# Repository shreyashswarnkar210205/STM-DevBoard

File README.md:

# ⚡ STM-OWN – Custom STM32 Development Board

Custom STM32-based development board designed in **KiCad** for learning and experimenting with embedded systems and PCB design.

This project demonstrates the complete PCB design workflow including schematic design, PCB layout, custom footprint creation, and hardware documentation.

---

## 🧠 Project Overview

**STM-OWN** is a custom STM32 development board inspired by common development boards such as Bluepill and Nucleo boards.

The objective of this project was to practice:

- STM32 hardware design
- Schematic capture
- PCB layout and routing
- Creating custom KiCad libraries
- Generating manufacturing-ready files
- Hardware documentation

This board can be used for:

- Embedded firmware development
- Peripheral interfacing
- Learning STM32 architecture
- Rapid prototyping

---

## 🛠 Tools Used

- **KiCad** – Schematic capture and PCB design
- **Custom symbol libraries**
- **Custom footprint libraries**
- **Git & GitHub** – Version control
- **PDF exports** – Documentation

---

## 🏗 PCB Design

Features of the board include:

- STM32 microcontroller core
- GPIO breakout headers
- Power regulation circuitry
- Programming/debug interface
- User interface components (buttons / LEDs)

Design considerations:

- Proper decoupling capacitors
- Clean power routing
- Ground plane usage
- Optimized component placement
- Design Rule Check (DRC) compliance

---

## 🖼 Board Preview

### Front View

### Back View

### 3D View

---

## 📂 Repository Structure
STM-OWN
│
├── Main/ # KiCad project files
│ ├── Main.kicad_pcb
│ ├── Main.kicad_pro
│ └── backups/
│
├── SIGN.pretty/ # Custom footprint library
│
├── FRONT.png # PCB front render
├── BACK.png # PCB back render
├── ANGLE-1.png # 3D board view
├── ANGLE-2.png # 3D board view
│
├── Schematic.pdf # Full schematic
├── Layout.pdf # PCB layout documentation
├── Basic.pdf # Design notes
│
└── README.md

---

## 📑 Documentation

Included design documentation:

- **Schematic.pdf** – Full circuit schematic
- **Layout.pdf** – PCB layout visualization
- **Basic.pdf** – Additional design notes

These files allow quick viewing of the design without opening KiCad.

---

## 🎯 Learning Outcomes

Through this project:

- Designed a complete STM32 hardware platform
- Learned PCB routing and layout techniques
- Created custom KiCad footprints and symbols
- Generated fabrication-ready design files
- Practiced professional hardware documentation

---

## 🚀 Future Improvements

Possible upgrades for the next revision:

- Add USB programming interface
- Add SWD debugging header
- Improve power regulation efficiency
- Add additional peripheral connectors
- Convert to a 4-layer PCB design

---

## 📜 License

This project is open hardware and available for educational and experimental use.

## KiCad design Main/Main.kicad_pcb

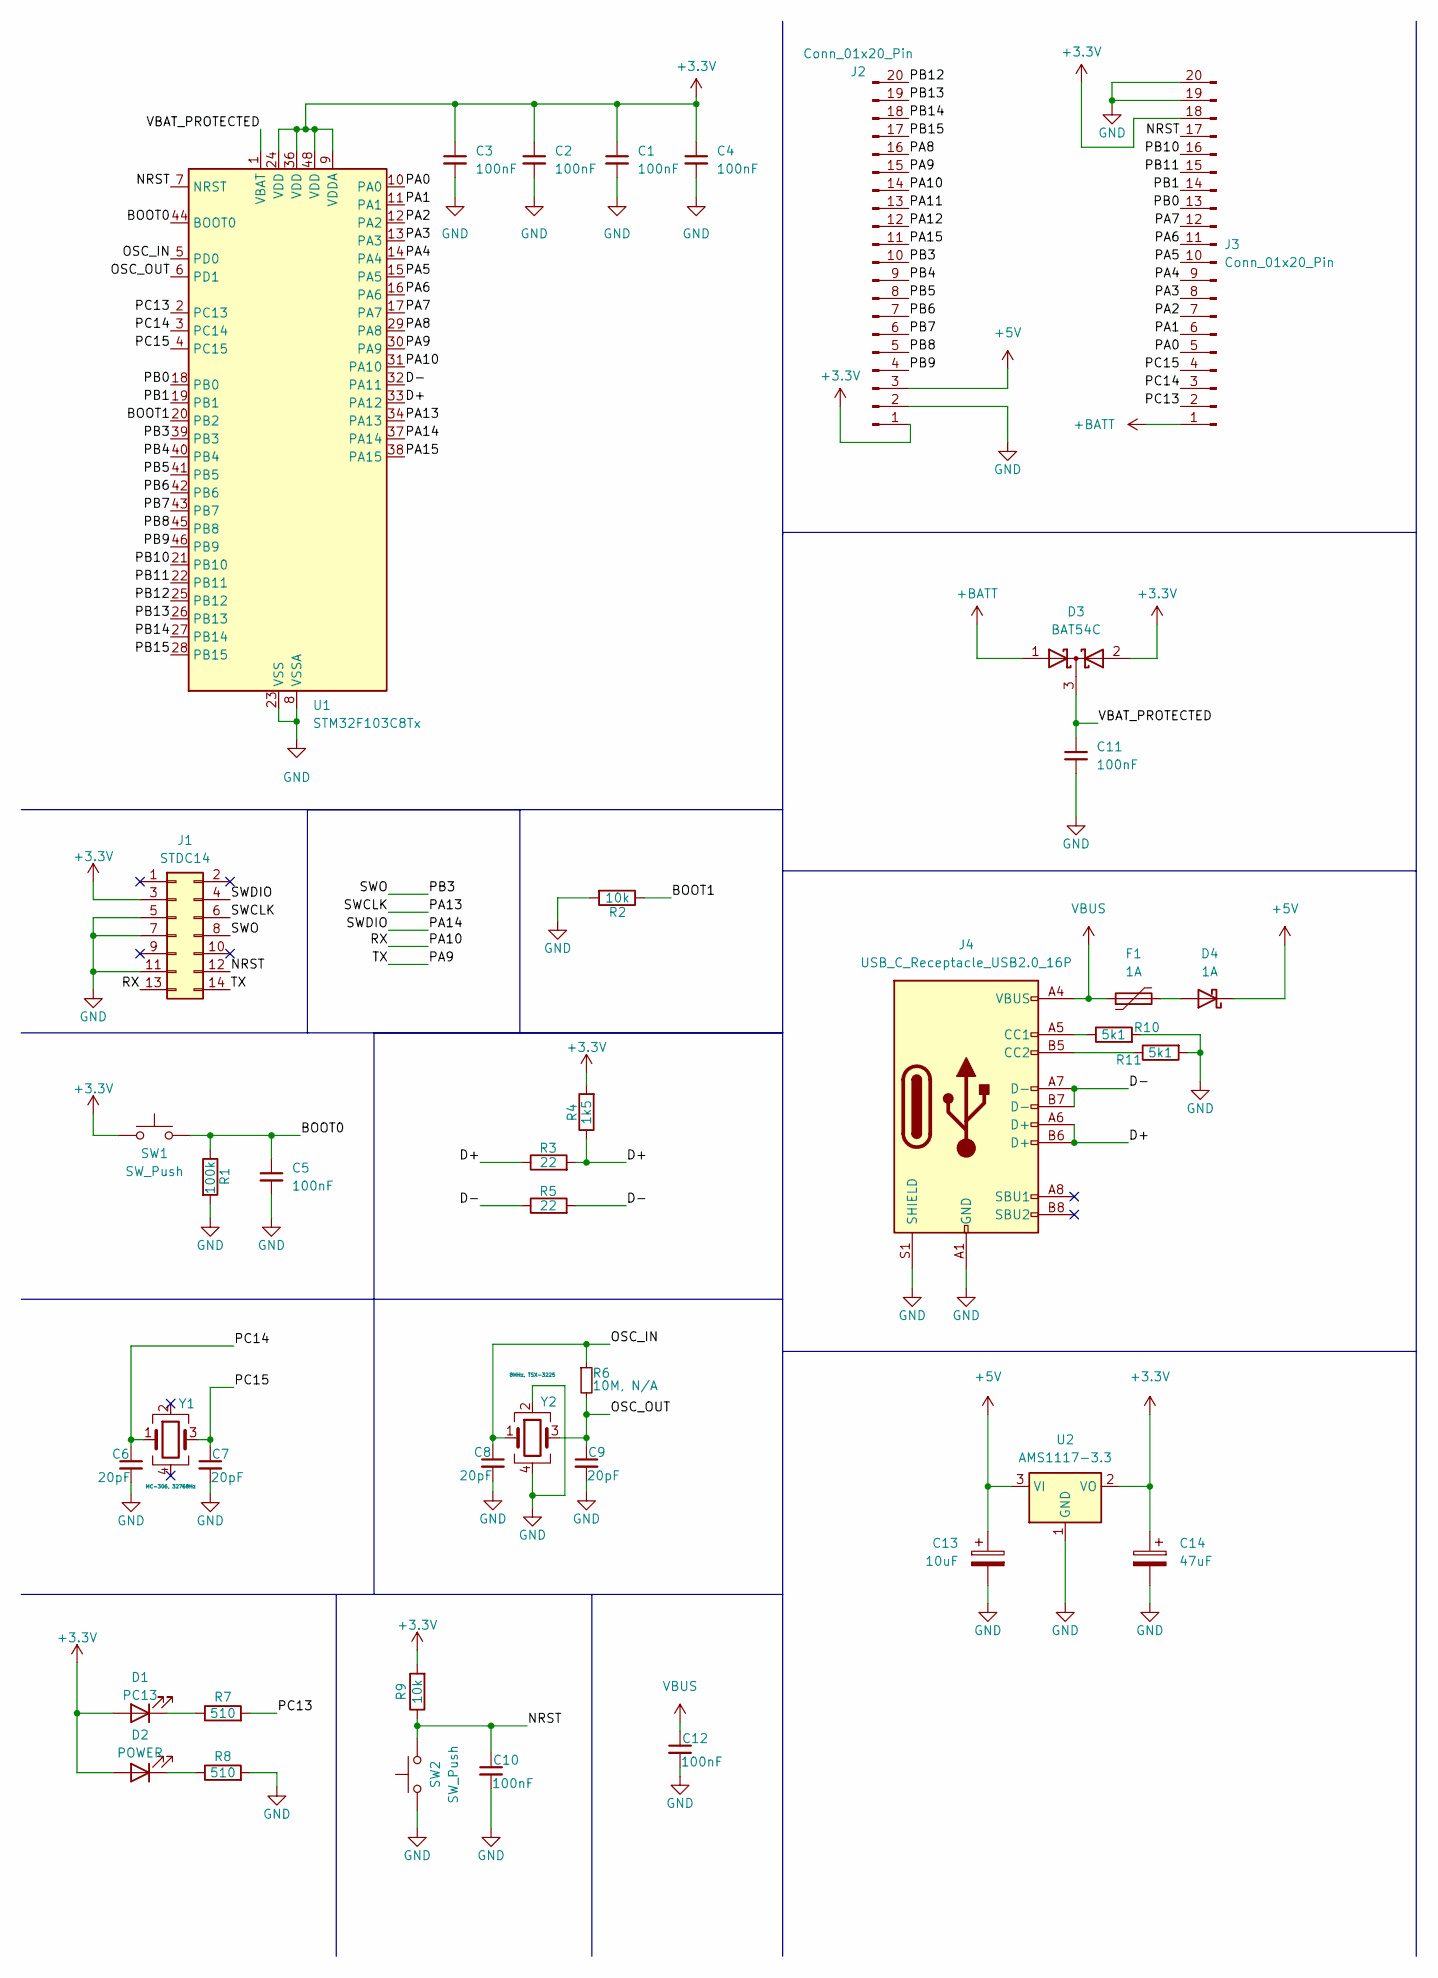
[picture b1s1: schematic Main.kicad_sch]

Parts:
C1, C2, C3, C4, C5, C10, C11, C12: 100nF; C_0402_1005Metric
C6, C7, C8, C9: 20pF; C_0402_1005Metric
C13: 10uF; CP_EIA-1608-08_AVX-J
C14: 47uF; CP_EIA-1608-08_AVX-J
D1: PC13; LED_2010_5025Metric
D2: POWER; LED_2010_5025Metric
D3: BAT54C; SOT-23
D4: 1A; D_1812_4532Metric_Pad1.30x3.40mm_HandSolder
F1: 1A; D_1812_4532Metric_Pad1.30x3.40mm_HandSolder
J1: STDC14; PinSocket_2x07_P2.54mm_Vertical
J2, J3: Conn_01x20_Pin; PinSocket_1x20_P2.54mm_Vertical
J4: USB_C_Receptacle_USB2.0_16P; USB_C_Receptacle_GCT_USB4105-xx-A_16P_TopMnt_Horizontal
R1: 100k; R_0201_0603Metric_Pad0.64x0.40mm_HandSolder
R2, R9: 10k; R_0201_0603Metric_Pad0.64x0.40mm_HandSolder
R3, R5: 22; R_0201_0603Metric_Pad0.64x0.40mm_HandSolder
R4: 1k5; R_0201_0603Metric_Pad0.64x0.40mm_HandSolder
R6: 10M, N/A; R_0201_0603Metric_Pad0.64x0.40mm_HandSolder
R7, R8: 510; R_0201_0603Metric_Pad0.64x0.40mm_HandSolder
R10, R11: 5k1; R_0201_0603Metric_Pad0.64x0.40mm_HandSolder
SW1, SW2: SW_Push; SW_Push_1P1T_NO_CK_KMR2
U1: STM32F103C8Tx; LQFP-48_7x7mm_P0.5mm
U2: AMS1117-3.3; SOT-223-3_TabPin2
Y1: MC-306, 32768Hz; Oscillator_SMD_Abracon_ASE-4Pin_3.2x2.5mm_HandSoldering
Y2: 8MHz, TSX-3225; Oscillator_SMD_Abracon_ASE-4Pin_3.2x2.5mm_HandSoldering

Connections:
+3.3V: C1.1, C2.1, C3.1, C4.1, C14.1, D1.2 (A), D2.2 (A), D3.2 (A), J1.3, J2.1, J3.18, R4.2, R9.2, SW1.1, U1.9 (VDDA), U1.24 (VDD), U1.36 (VDD), U1.48 (VDD), U2.2 (VO)
+5V: C13.1, D4.1 (K), J2.3, U2.3 (VI)
+BATT: D3.1 (A), J3.1
/BOOT0: C5.1, R1.1, SW1.2, U1.44 (BOOT0)
/BOOT1: R2.1, U1.20 (PB2)
/D+: J4.A6 (D+), J4.B6 (D+), R3.1, R3.2, R4.1, U1.33 (PA12)
/D-: J4.A7 (D-), J4.B7 (D-), R5.1, R5.2, U1.32 (PA11)
/NRST: C10.1, J1.12, J3.17, R9.1, SW2.2, U1.7 (NRST)
/OSC_IN: C8.1, R6.1, U1.5 (PD0), Y2.1
/OSC_OUT: C9.1, R6.2, U1.6 (PD1), Y2.3
/PA0: J3.5, U1.10 (PA0)
/PA1: J3.6, U1.11 (PA1)
/PA2: J3.7, U1.12 (PA2)
/PA3: J3.8, U1.13 (PA3)
/PA4: J3.9, U1.14 (PA4)
/PA5: J3.10, U1.15 (PA5)
/PA6: J3.11, U1.16 (PA6)
/PA7: J3.12, U1.17 (PA7)
/PA8: J2.16, U1.29 (PA8)
/PA9: J1.14, J2.15, U1.30 (PA9)
/PA10: J1.13, J2.14, U1.31 (PA10)
/PA11: J2.13
/PA12: J2.12
/PA13: J1.6, U1.34 (PA13)
/PA14: J1.4, U1.37 (PA14)
/PA15: J2.11, U1.38 (PA15)
/PB0: J3.13, U1.18 (PB0)
/PB1: J3.14, U1.19 (PB1)
/PB3: J1.8, J2.10, U1.39 (PB3)
/PB4: J2.9, U1.40 (PB4)
/PB5: J2.8, U1.41 (PB5)
/PB6: J2.7, U1.42 (PB6)
/PB7: J2.6, U1.43 (PB7)
/PB8: J2.5, U1.45 (PB8)
/PB9: J2.4, U1.46 (PB9)
/PB10: J3.16, U1.21 (PB10)
/PB11: J3.15, U1.22 (PB11)
/PB12: J2.20, U1.25 (PB12)
/PB13: J2.19, U1.26 (PB13)
/PB14: J2.18, U1.27 (PB14)
/PB15: J2.17, U1.28 (PB15)
/PC13: J3.2, R7.2, U1.2 (PC13)
/PC14: C6.1, J3.3, U1.3 (PC14), Y1.1
/PC15: C7.1, J3.4, U1.4 (PC15), Y1.3
/VBAT_PROTECTED: C11.1, D3.3 (K), U1.1 (VBAT)
GND: C1.2, C2.2, C3.2, C4.2, C5.2, C6.2, C7.2, C8.2, C9.2, C10.2, C11.2, C12.2, C13.2, C14.2, J1.5, J1.7, J1.11, J2.2, J3.19, J3.20, J4.A1 (GND), J4.A12 (GND), J4.B1 (GND), J4.B12 (GND), J4.S1 (SHIELD), R1.2, R2.2, R8.2, R10.2, R11.2, SW2.1, U1.8 (VSSA), U1.23 (VSS), U1.35 (VSS), U1.47 (VSS), U2.1 (GND), Y2.2, Y2.4
unnamed: D1.1 (K), R7.1
unnamed: D2.1 (K), R8.1
unnamed: D4.2 (A), F1.2
unnamed: J4.A5 (CC1), R10.1
unnamed: J4.B5 (CC2), R11.1
VBUS: C12.1, F1.1, J4.A4 (VBUS), J4.A9 (VBUS), J4.B4 (VBUS), J4.B9 (VBUS)

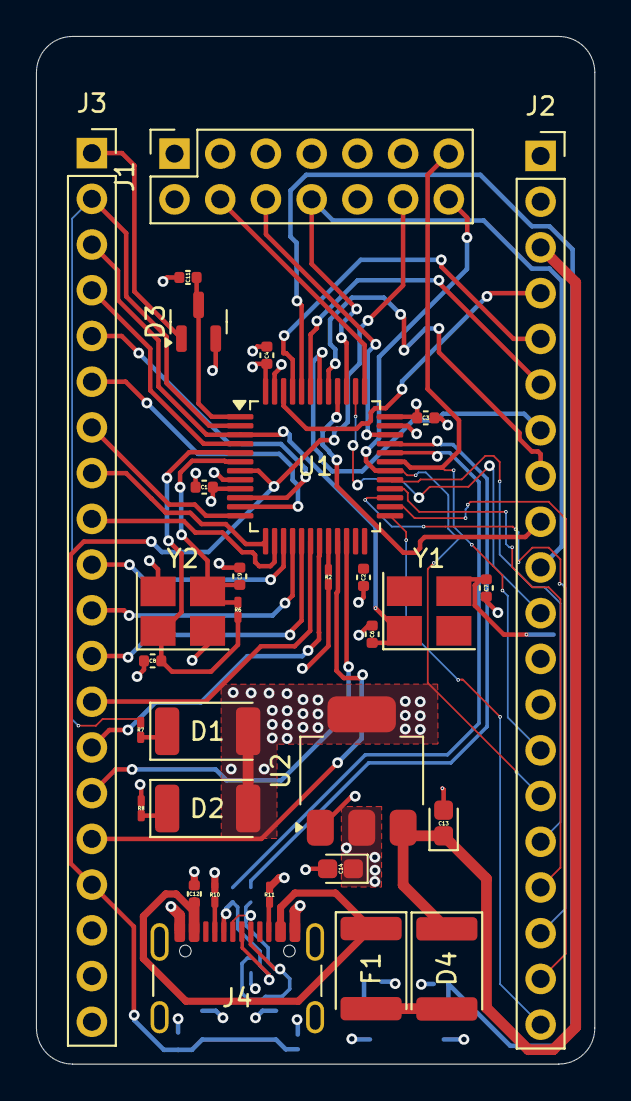
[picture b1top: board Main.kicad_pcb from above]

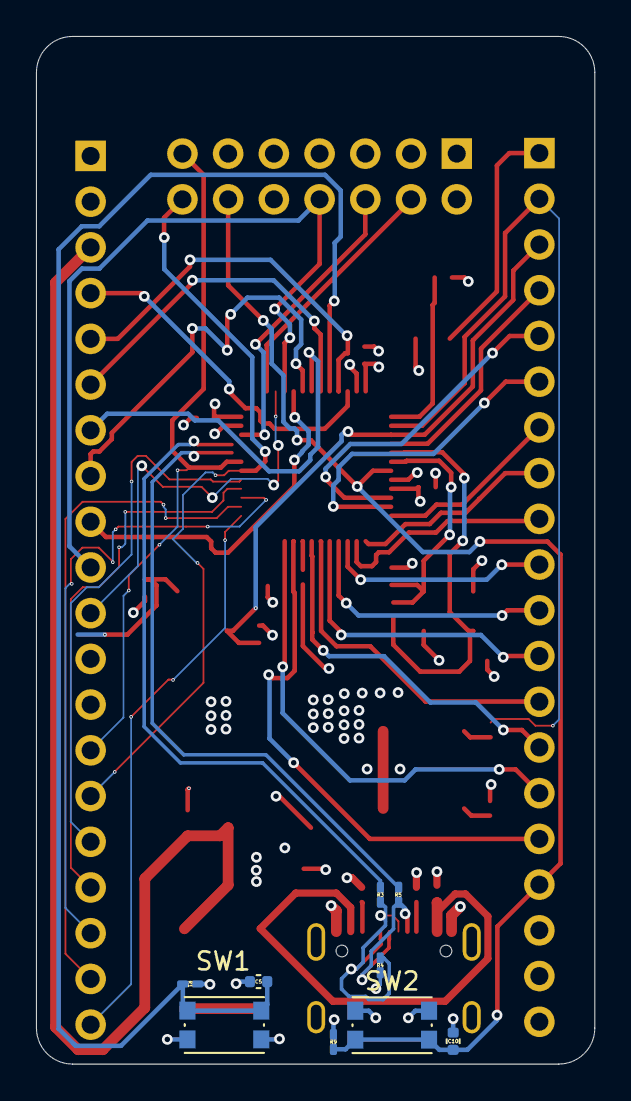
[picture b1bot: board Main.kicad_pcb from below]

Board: 4 copper layers, 31.0 x 57.1 mm, 40 parts (9 on the bottom side), 50 nets.

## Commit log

2026-03-09 Second Commit
2026-03-09 Third Commit
2026-03-09 Fourth Commit
